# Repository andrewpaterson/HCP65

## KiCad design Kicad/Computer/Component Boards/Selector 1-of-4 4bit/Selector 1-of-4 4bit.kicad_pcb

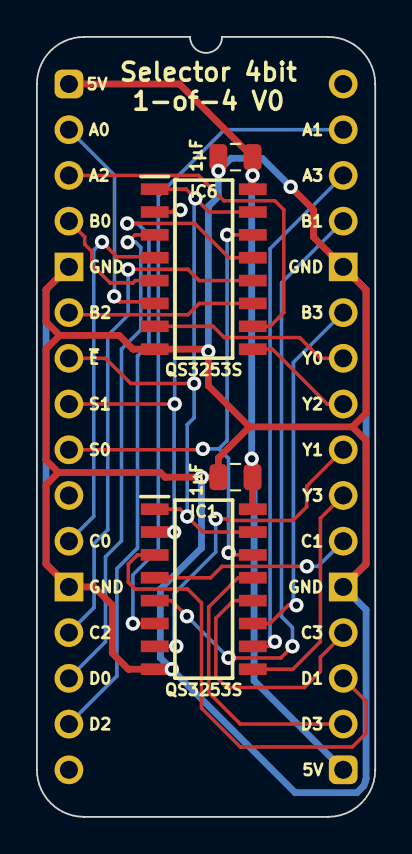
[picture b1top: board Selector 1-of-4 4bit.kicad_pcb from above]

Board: 2 copper layers, 18.8 x 43.3 mm, 5 parts (0 on the bottom side), 25 nets.

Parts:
C1, C3: 1μF; C_0805
IC1, IC6: QS3253S1G; SOIC127P602X173-16N
J2: Board 2x16 W15.24mm; DIP-32_Board_W15.24mm

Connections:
5V: C1.1, C3.1, IC1.16 (5V), IC6.16 (5V), J2.1, J2.17
A0: IC6.6 (I0A), J2.2
A1: IC1.6 (I0A), J2.31
A2: IC6.10 (I0B), J2.3
A3: IC1.10 (I0B), J2.30
B0: IC6.5 (I1A), J2.4
B1: IC1.5 (I1A), J2.29
B2: IC6.11 (I1B), J2.6
B3: IC1.11 (I1B), J2.27
C0: IC6.4 (I2A), J2.11
C1: IC1.4 (I2A), J2.22
C2: IC6.12 (I2B), J2.13
C3: IC1.12 (I2B), J2.20
D0: IC6.3 (I3A), J2.14
D1: IC1.3 (I3A), J2.19
D2: IC6.13 (I3B), J2.15
D3: IC1.13 (I3B), J2.18
GND: C1.2, C3.2, IC1.8 (GND), IC6.8 (GND), J2.5, J2.12, J2.21, J2.28
S0: IC1.14 (S0), IC6.14 (S0), J2.9
S1: IC1.2 (S1), IC6.2 (S1), J2.8
Y0: IC6.7 (YA), J2.26
Y1: IC1.7 (YA), J2.24
Y2: IC6.9 (YB), J2.25
Y3: IC1.9 (YB), J2.23
~E: IC1.1 (~EA), IC1.15 (~EB), IC6.1 (~EA), IC6.15 (~EB), J2.7

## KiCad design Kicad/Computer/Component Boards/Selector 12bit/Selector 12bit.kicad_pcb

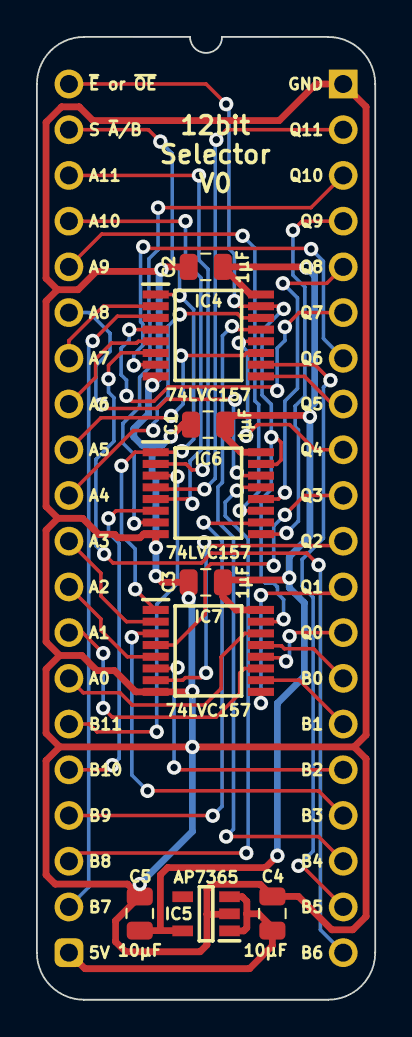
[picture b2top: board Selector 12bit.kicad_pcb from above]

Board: 2 copper layers, 18.8 x 53.5 mm, 10 parts (0 on the bottom side), 41 nets.

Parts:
C1, C2, C3: 1μF; C_0805
C4, C5: 10µF; C_0805
IC4, IC6, IC7: 74LVC157APW,118; SOP65P640X110-16N
IC5: AP7365-33WG-7; SOT95P285X130-5N
J1: Board 2x20 W15.24mm; DIP-40_Board_W15.24mm_Alt

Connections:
5V: C4.1, IC5.1 (6VIn), IC5.3 (EN), J1.20
/3.3V: C1.1, C2.1, C3.1, C5.1, IC4.16 (3V), IC5.5 (3.3VOut), IC6.16 (3V), IC7.16 (3V)
A0: IC7.14 (4I0), J1.14
A1: IC7.11 (3I0), J1.13
A2: IC7.5 (2I0), J1.12
A3: IC7.2 (1I0), J1.11
A4: IC4.14 (4I0), J1.10
A5: IC4.11 (3I0), J1.9
A6: IC4.5 (2I0), J1.8
A7: IC4.2 (1I0), J1.7
A8: IC6.14 (4I0), J1.6
A9: IC6.11 (3I0), J1.5
A10: IC6.5 (2I0), J1.4
A11: IC6.2 (1I0), J1.3
B0: IC7.13 (4I1), J1.27
B1: IC7.10 (3I1), J1.26
B2: IC7.6 (2I1), J1.25
B3: IC7.3 (1I1), J1.24
B4: IC4.13 (4I1), J1.23
B5: IC4.10 (3I1), J1.22
B6: IC4.6 (2I1), J1.21
B7: IC4.3 (1I1), J1.19
B8: IC6.13 (4I1), J1.18
B9: IC6.10 (3I1), J1.17
B10: IC6.6 (2I1), J1.16
B11: IC6.3 (1I1), J1.15
GND: C1.2, C2.2, C3.2, C4.2, C5.2, IC4.8 (GND), IC5.2 (GND), IC6.8 (GND), IC7.8 (GND), J1.40
Q0: IC7.12 (4Y), J1.28
Q1: IC7.9 (3Y), J1.29
Q2: IC7.7 (2Y), J1.30
Q3: IC7.4 (1Y), J1.31
Q4: IC4.12 (4Y), J1.32
Q5: IC4.9 (3Y), J1.33
Q6: IC4.7 (2Y), J1.34
Q7: IC4.4 (1Y), J1.35
Q8: IC6.12 (4Y), J1.36
Q9: IC6.9 (3Y), J1.37
Q10: IC6.7 (2Y), J1.38
Q11: IC6.4 (1Y), J1.39
S: IC4.1 (S), IC6.1 (S), IC7.1 (S), J1.2
~E: IC4.15 (~E), IC6.15 (~E), IC7.15 (~E), J1.1

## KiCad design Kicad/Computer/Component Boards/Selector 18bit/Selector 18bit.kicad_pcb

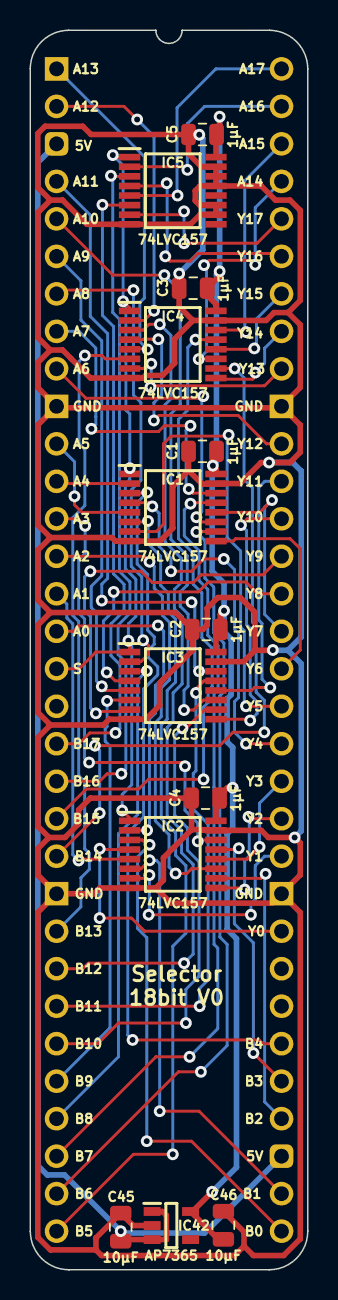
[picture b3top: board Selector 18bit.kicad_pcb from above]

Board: 2 copper layers, 18.8 x 84.0 mm, 14 parts (0 on the bottom side), 58 nets.

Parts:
C1, C2, C3, C4, C5: 1μF; C_0805
C45, C46: 10μF; C_0805
IC1, IC2, IC3, IC4, IC5: 74LVC157APW,118; SOP65P640X110-16N
IC42: AP7365-33WG-7; SOT95P285X130-5N
J2: Board 2x32 W15.24mm; DIP-64_Board_W15.24mm

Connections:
5V: C45.1, IC42.1 (6VIn), IC42.3 (EN), J2.3, J2.35
/3.3V: C1.1, C2.1, C3.1, C4.1, C5.1, C46.1, IC1.16 (3V), IC2.16 (3V), IC3.16 (3V), IC4.16 (3V), IC5.16 (3V), IC42.5 (3.3VOut)
A0: IC2.2 (1I0), J2.16
A1: IC2.5 (2I0), J2.15
A2: IC2.11 (3I0), J2.14
A3: IC2.14 (4I0), J2.13
A4: IC1.2 (1I0), J2.12
A5: IC1.5 (2I0), J2.11
A6: IC1.11 (3I0), J2.9
A7: IC1.14 (4I0), J2.8
A8: IC3.2 (1I0), J2.7
A9: IC3.5 (2I0), J2.6
A10: IC3.11 (3I0), J2.5
A11: IC3.14 (4I0), J2.4
A12: IC4.2 (1I0), J2.2
A13: IC4.5 (2I0), J2.1
A14: IC4.11 (3I0), J2.61
A15: IC4.14 (4I0), J2.62
A16: IC5.2 (1I0), J2.63
A17: IC5.5 (2I0), J2.64
B0: IC2.3 (1I1), J2.33
B1: IC2.6 (2I1), J2.34
B2: IC2.10 (3I1), J2.36
B3: IC2.13 (4I1), J2.37
B4: IC1.3 (1I1), J2.38
B5: IC1.6 (2I1), J2.32
B6: IC1.10 (3I1), J2.31
B7: IC1.13 (4I1), J2.30
B8: IC3.3 (1I1), J2.29
B9: IC3.6 (2I1), J2.28
B10: IC3.10 (3I1), J2.27
B11: IC3.13 (4I1), J2.26
B12: IC4.3 (1I1), J2.25
B13: IC4.6 (2I1), J2.24
B14: IC4.10 (3I1), J2.22
B15: IC4.13 (4I1), J2.21
B16: IC5.3 (1I1), J2.20
B17: IC5.6 (2I1), J2.19
GND: C1.2, C2.2, C3.2, C4.2, C5.2, C45.2, C46.2, IC1.8 (GND), IC1.15 (~E), IC2.8 (GND), IC2.15 (~E), IC3.8 (GND), IC3.15 (~E), IC4.8 (GND), IC4.15 (~E), IC5.8 (GND), IC5.10 (3I1), IC5.11 (3I0), IC5.13 (4I1), IC5.14 (4I0), IC5.15 (~E), IC42.2 (GND), J2.10, J2.23, J2.42, J2.55
S: IC1.1 (S), IC2.1 (S), IC3.1 (S), IC4.1 (S), IC5.1 (S), J2.17
Y0: IC2.4 (1Y), J2.41
Y1: IC2.7 (2Y), J2.43
Y2: IC2.9 (3Y), J2.44
Y3: IC2.12 (4Y), J2.45
Y4: IC1.4 (1Y), J2.46
Y5: IC1.7 (2Y), J2.47
Y6: IC1.9 (3Y), J2.48
Y7: IC1.12 (4Y), J2.49
Y8: IC3.4 (1Y), J2.50
Y9: IC3.7 (2Y), J2.51
Y10: IC3.9 (3Y), J2.52
Y11: IC3.12 (4Y), J2.53
Y12: IC4.4 (1Y), J2.54
Y13: IC4.7 (2Y), J2.56
Y14: IC4.9 (3Y), J2.57
Y15: IC4.12 (4Y), J2.58
Y16: IC5.4 (1Y), J2.59
Y17: IC5.7 (2Y), J2.60

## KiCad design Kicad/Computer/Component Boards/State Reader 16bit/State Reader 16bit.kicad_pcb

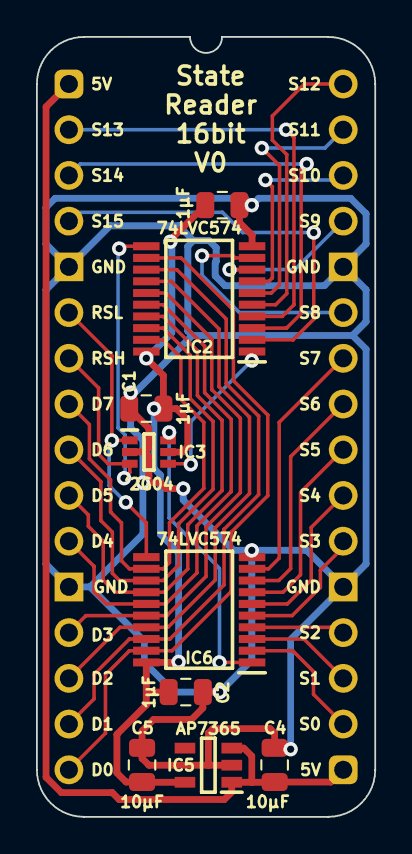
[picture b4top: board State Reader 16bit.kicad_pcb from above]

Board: 2 copper layers, 18.8 x 43.3 mm, 10 parts (0 on the bottom side), 31 nets.

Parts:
C1, C2, C9: 1μF; C_0805
C4, C5: 10µF; C_0805
IC2, IC6: 74LVC574APW,118; SOP65P640X110-20N
IC3: 74LVC2G04GW-Q100H; SOP65P210X110-6N
IC5: AP7365-33WG-7; SOT95P285X130-5N
J1: Board 2x16 W15.24mm; DIP-32_Board_W15.24mm

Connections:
5V: C4.1, IC5.1 (6VIn), IC5.3 (EN), J1.1, J1.17
/3.3V: C1.1, C2.1, C5.1, C9.1, IC2.20 (3V), IC3.5 (3V), IC5.5 (3.3VOut), IC6.20 (3V)
/~Read State High: IC2.1 (~OE), IC3.4 (2Y)
/~Read State Low: IC3.6 (1Y), IC6.1 (~OE)
D0: IC2.12 (Q7), IC6.19 (Q0), J1.16
D1: IC2.13 (Q6), IC6.18 (Q1), J1.15
D2: IC2.14 (Q5), IC6.17 (Q2), J1.14
D3: IC2.15 (Q4), IC6.16 (Q3), J1.13
D4: IC2.16 (Q3), IC6.15 (Q4), J1.11
D5: IC2.17 (Q2), IC6.14 (Q5), J1.10
D6: IC2.18 (Q1), IC6.13 (Q6), J1.9
D7: IC2.19 (Q0), IC6.12 (Q7), J1.8
GND: C1.2, C2.2, C4.2, C5.2, C9.2, IC2.10 (GND), IC3.2 (GND), IC5.2 (GND), IC6.10 (GND), J1.5, J1.12, J1.21, J1.28
Read State High: IC2.11 (CP), IC3.3 (2A), J1.7
Read State Low: IC3.1 (1A), IC6.11 (CP), J1.6
S0: IC6.2 (D0), J1.18
S1: IC6.3 (D1), J1.19
S2: IC6.4 (D2), J1.20
S3: IC6.5 (D3), J1.22
S4: IC6.6 (D4), J1.23
S5: IC6.7 (D5), J1.24
S6: IC6.8 (D6), J1.25
S7: IC6.9 (D7), J1.26
S8: IC2.9 (D7), J1.27
S9: IC2.8 (D6), J1.29
S10: IC2.7 (D5), J1.30
S11: IC2.6 (D4), J1.31
S12: IC2.5 (D3), J1.32
S13: IC2.4 (D2), J1.2
S14: IC2.3 (D1), J1.3
S15: IC2.2 (D0), J1.4

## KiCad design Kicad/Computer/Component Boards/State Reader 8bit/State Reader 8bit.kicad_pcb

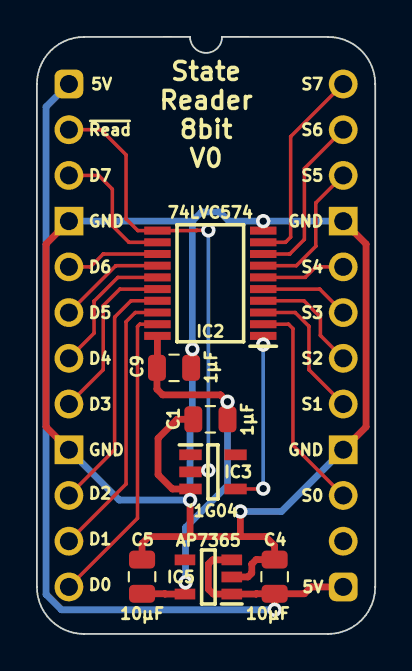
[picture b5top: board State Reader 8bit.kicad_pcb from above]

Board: 2 copper layers, 18.8 x 33.2 mm, 8 parts (0 on the bottom side), 21 nets.

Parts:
C1, C9: 1μF; C_0805
C4, C5: 10µF; C_0805
IC2: 74LVC574APW,118; SOP65P640X110-20N
IC3: 74LVC1G04GV,125; SOT95P275X110-5N
IC5: AP7365-33WG-7; SOT95P285X130-5N
J1: Board 2x12 W15.24mm; DIP-24_Board_W15.24mm

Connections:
5V: C4.1, IC5.1 (6VIn), IC5.3 (EN), J1.1, J1.13
/3.3V: C1.1, C5.1, C9.1, IC2.20 (3V), IC5.5 (3.3VOut)
/~Read State: IC2.1 (~OE), IC3.4 (Y)
D0: IC2.19 (Q0), J1.12
D1: IC2.18 (Q1), J1.11
D2: IC2.17 (Q2), J1.10
D3: IC2.16 (Q3), J1.8
D4: IC2.15 (Q4), J1.7
D5: IC2.14 (Q5), J1.6
D6: IC2.13 (Q6), J1.5
D7: IC2.12 (Q7), J1.3
GND: C1.2, C4.2, C5.2, C9.2, IC2.10 (GND), IC3.3 (GND), IC5.2 (GND), J1.4, J1.9, J1.16, J1.21
Read State: IC2.11 (CP), IC3.2 (A), J1.2
S0: IC2.2 (D0), J1.15
S1: IC2.3 (D1), J1.17
S2: IC2.4 (D2), J1.18
S3: IC2.5 (D3), J1.19
S4: IC2.6 (D4), J1.20
S5: IC2.7 (D5), J1.22
S6: IC2.8 (D6), J1.23
S7: IC2.9 (D7), J1.24

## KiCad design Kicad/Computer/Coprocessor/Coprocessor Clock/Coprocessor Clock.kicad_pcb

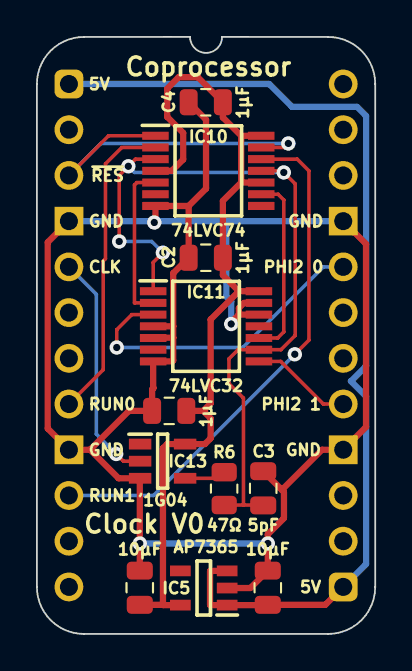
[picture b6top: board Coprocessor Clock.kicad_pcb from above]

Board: 2 copper layers, 18.8 x 33.2 mm, 12 parts (0 on the bottom side), 13 nets.

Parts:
C1, C2, C4: 1μF; C_0805
C3: 5pF; C_0805
C8, C9: 10µF; C_0805
IC5: AP7365-33WG-7; SOT95P285X130-5N
IC10: 74LVC74APW,118; SOP65P640X110-14N
IC11: 74LVC32APW,118; SOP65P640X110-14N
IC13: 74LVC1G04GV,125; SOT95P275X110-5N
J2: Board 2x12 W15.24mm; DIP-24_Board_W15.24mm
R6: 47Ω; R_0805

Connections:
5V: C8.1, IC5.1 (6VIn), IC5.3 (EN), J2.1, J2.13
40MHz: IC13.2 (A), J2.5
/3.3V: C1.1, C2.1, C4.1, C9.1, IC5.5 (3.3VOut), IC10.4 (~1SD), IC10.10 (~2SD), IC10.14 (3V), IC11.14 (3V), IC13.5 (3V)
/40MHz_{0,1}: C3.1, IC10.3 (1CP), IC10.11 (2CP), IC11.1 (1A), IC11.9 (3A), R6.1
CPHI2_{0}: IC11.3 (1Y), J2.20
CPHI2_{1}: IC11.8 (3Y), J2.17
CRun0: IC10.2 (1D), J2.8
CRun1: IC10.12 (2D), J2.10
GND: C1.2, C2.2, C3.2, C4.2, C8.2, C9.2, IC5.2 (GND), IC10.7 (GND), IC11.4 (2A), IC11.5 (2B), IC11.7 (GND), IC11.12 (4A), IC11.13 (4B), IC13.3 (GND), J2.4, J2.9, J2.16, J2.21
unnamed: IC10.5 (1Q), IC11.2 (1B)
unnamed: IC10.9 (2Q), IC11.10 (3B)
unnamed: IC13.4 (Y), R6.2
~Reset: IC10.1 (~1RD), IC10.13 (~2RD), J2.3

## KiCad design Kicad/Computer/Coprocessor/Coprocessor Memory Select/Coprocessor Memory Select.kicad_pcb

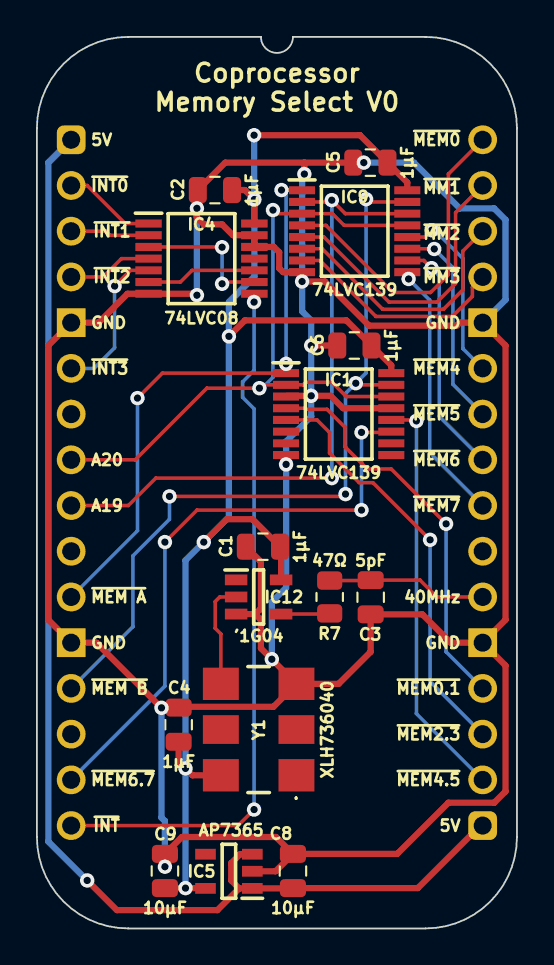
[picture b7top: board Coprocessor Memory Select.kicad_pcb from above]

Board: 2 copper layers, 26.7 x 49.5 mm, 16 parts (0 on the bottom side), 29 nets.

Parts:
C1, C2, C4, C5, C6: 1μF; C_0805
C3: 5pF; C_0805
C8, C9: 10µF; C_0805
IC1, IC9: 74LVC139PW,118; SOP65P640X110-16N
IC4: 74LVC08APW,112; SOP65P640X110-14N
IC5: AP7365-33WG-7; SOT95P285X130-5N
IC12: 74LVC1G04GV,125; SOT95P275X110-5N
J2: Board 2x16 W22.86mm; DIP-32_Board_W22.86mm
R7: 47Ω; R_0805
Y1: XLH735040.000000I; XLH736074250000I

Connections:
5V: C8.1, IC5.1 (6VIn), IC5.3 (EN), J2.1, J2.17
40MHz: C3.1, J2.22, R7.1
/3.3V: C1.1, C2.1, C4.1, C5.1, C6.1, C9.1, IC1.16 (3V), IC4.14 (3V), IC5.5 (3.3VOut), IC9.16 (3V), IC12.5 (3V), Y1.6 (3V)
/~40MHz: IC12.2 (A), Y1.4 (OUT)
/~INT0•1: IC4.3 (1Y), IC4.9 (3A)
/~INT2•3: IC4.6 (2Y), IC4.10 (3B)
AM19: IC9.2 (1A0), IC9.14 (2A0), J2.9
AM20: IC1.2 (1A0), IC1.14 (2A0), IC9.3 (1A1), IC9.13 (2A1), J2.8
GND: C1.2, C2.2, C3.2, C4.2, C5.2, C6.2, C8.2, C9.2, IC1.3 (1A1), IC1.8 (GND), IC1.13 (2A1), IC4.7 (GND), IC4.12 (4A), IC4.13 (4B), IC5.2 (GND), IC9.8 (GND), IC12.3 (GND), J2.5, J2.12, J2.21, J2.28, Y1.3 (GND)
M~Memory0: IC9.4 (~1Y0), J2.32
M~Memory0•1: IC1.4 (~1Y0), J2.20
M~Memory1: IC9.5 (~1Y1), J2.31
M~Memory2: IC9.6 (~1Y2), J2.30
M~Memory2•3: IC1.5 (~1Y1), J2.19
M~Memory3: IC9.7 (~1Y3), J2.29
M~Memory4: IC9.12 (~2Y0), J2.27
M~Memory4•5: IC1.12 (~2Y0), J2.18
M~Memory5: IC9.11 (~2Y1), J2.26
M~Memory6: IC9.10 (~2Y2), J2.25
M~Memory6•7: IC1.11 (~2Y1), J2.15
M~Memory7: IC9.9 (~2Y3), J2.24
unnamed: IC12.4 (Y), R7.2
~INT0: IC4.1 (1A), J2.2
~INT1: IC4.2 (1B), J2.3
~INT2: IC4.4 (2A), J2.4
~INT3: IC4.5 (2B), J2.6
~INT: IC4.8 (3Y), J2.16
~Memory A: IC1.1 (~1E), IC9.1 (~1E), J2.11
~Memory B: IC1.15 (~2E), IC9.15 (~2E), J2.13

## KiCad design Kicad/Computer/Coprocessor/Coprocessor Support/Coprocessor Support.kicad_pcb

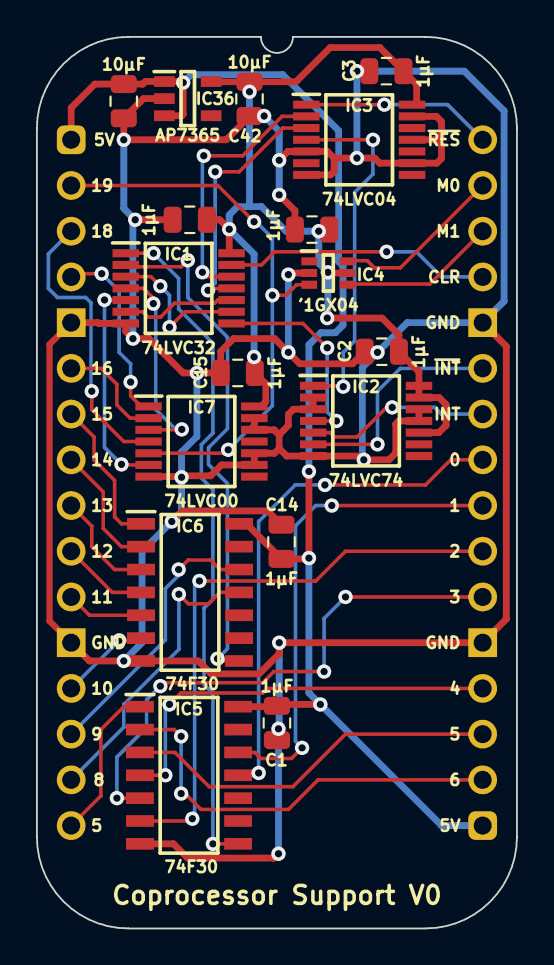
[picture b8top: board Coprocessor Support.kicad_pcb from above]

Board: 2 copper layers, 26.7 x 49.5 mm, 18 parts (0 on the bottom side), 39 nets.

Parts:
C1, C2, C3, C12, C13, C14, C15: 1µF; C_0805
C41, C42: 10μF; C_0805
IC1: 74LVC32APW,118; SOP65P640X110-14N
IC2: 74LVC74APW,118; SOP65P640X110-14N
IC3: 74LVC04APW,118; SOP65P640X110-14N
IC4: 74LVC1GX04GW,125; SOP65P210X110-6N
IC5, IC6: SN74F30DR; SOIC127P600X175-14N
IC7: 74LVC00APW,112; SOP65P640X110-14N
IC36: AP7365-33WG-7; SOT95P285X130-5N
J7: Board 2x16 W22.86mm; DIP-32_Board_W22.86mm

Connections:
5V: C1.1, C14.1, C41.1, IC5.14 (5V), IC6.14 (5V), IC36.1 (6VIn), IC36.3 (EN), J7.1, J7.17
/3.3V: C2.1, C3.1, C12.1, C13.1, C15.1, C42.1, IC1.14 (3V), IC2.10 (~2SD), IC2.13 (~2RD), IC2.14 (3V), IC3.14 (3V), IC4.5 (3V), IC7.14 (3V), IC36.5 (3.3VOut)
/RD: IC1.11 (4Y), IC3.3 (2A)
/Reset: IC1.12 (4A), IC3.2 (1Y)
/~AB: IC1.3 (1Y), IC1.9 (3A)
/~CAAA: IC1.1 (1A), IC5.8 (Y)
/~CAAB: IC1.2 (1B), IC6.8 (Y)
/~CAAC: IC1.4 (2A), IC7.3 (1Y)
/~CAAD: IC1.5 (2B), IC7.6 (2Y)
/~CATOP: IC1.8 (3Y), IC2.4 (~1SD)
/~CD: IC1.6 (2Y), IC1.10 (3B)
/~RD: IC2.1 (~1RD), IC3.4 (2Y)
CA0: IC5.11 (G), J7.25
CA1: IC5.12 (H), J7.24
CA2: IC5.6 (F), J7.23
CA3: IC5.5 (E), J7.22
CA4: IC5.4 (D), J7.20
CA5: IC5.3 (C), J7.19
CA6: IC5.2 (B), J7.18
CA7: IC5.1 (A), J7.16
CA8: IC6.11 (G), J7.15
CA9: IC6.12 (H), J7.14
CA10: IC6.6 (F), J7.13
CA11: IC6.5 (E), J7.11
CA12: IC6.4 (D), J7.10
CA13: IC6.3 (C), J7.9
CA14: IC6.2 (B), J7.8
CA15: IC6.1 (A), J7.7
CA16: IC7.2 (1B), J7.6
CA17: IC7.1 (1A), J7.4
CA18: IC7.4 (2A), J7.3
CA19: IC4.3 (X1), IC7.5 (2B), J7.2
CAMemory0: IC4.6 (Y), J7.31
CAMemory1: IC4.4 (~Y), J7.30
CLR: IC1.13 (4B), J7.29
GND: C1.2, C2.2, C3.2, C12.2, C13.2, C14.2, C15.2, C41.2, C42.2, IC1.7 (GND), IC2.2 (1D), IC2.3 (1CP), IC2.7 (GND), IC2.11 (2CP), IC2.12 (2D), IC3.5 (3A), IC3.7 (GND), IC3.9 (4A), IC3.11 (5A), IC3.13 (6A), IC4.2 (GND), IC5.7 (GND), IC6.7 (GND), IC7.7 (GND), IC7.9 (3A), IC7.10 (3B), IC7.12 (4A), IC7.13 (4B), IC36.2 (GND), J7.5, J7.12, J7.21, J7.28
INT: IC2.5 (1Q), J7.26
~INT: IC2.6 (~1Q), J7.27
~Reset: IC3.1 (1A), J7.32
